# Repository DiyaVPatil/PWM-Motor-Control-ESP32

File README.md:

# ESP32 PWM Motor Controller
A custom PCB-based motor controller designed in KiCad for efficient PWM speed control of brushed DC motors using an ESP32 microcontroller.

This project began as a perfboard prototype and was later redesigned as a custom printed circuit board to improve physical dimensions and manufacturability.

## Features
- ESP32-based PWM motor control
- Adjustable motor speed (0–100% duty cycle)
- Logic-level MOSFET driver stage
- Flyback diode protection
- Battery-powered operation (3.7 V Li-ion)
- Compact custom PCB designed in KiCad

## Hardware
1) ESP32 DevKit | Main microcontroller 
2) IRLB8748 | Logic-level N-channel MOSFET 
3) Schottky Diode | Flyback protection 
4) TP4056 | Li-ion charging module 
5) 3.7 V Li-ion Battery | Portable power source 
6) Coreless DC Motor | Demonstration load 

## Project Timeline

### Version 1
Perfboard prototype built from KiCad schematic as a "proof-of-concept"

### Version 2
Final custom KiCad PCB, after making improvements from the perfboard prototype. 

## Future Improvements

- Real-time speed feedback on an OLED display
- Battery percentage monitoring
- Current sensing
- Bluetooth control
- Closed-loop speed control using encoder feedback

## Repository Structure
Note that there is a functionality video available under images and BOM
```
ESP32-PWM-Motor-Controller/

firmware/
hardware/
kicad/
images and BOM/
docs/
README.md
```

## Author

Diya

Electrical Engineering Student  
University of California, Riverside

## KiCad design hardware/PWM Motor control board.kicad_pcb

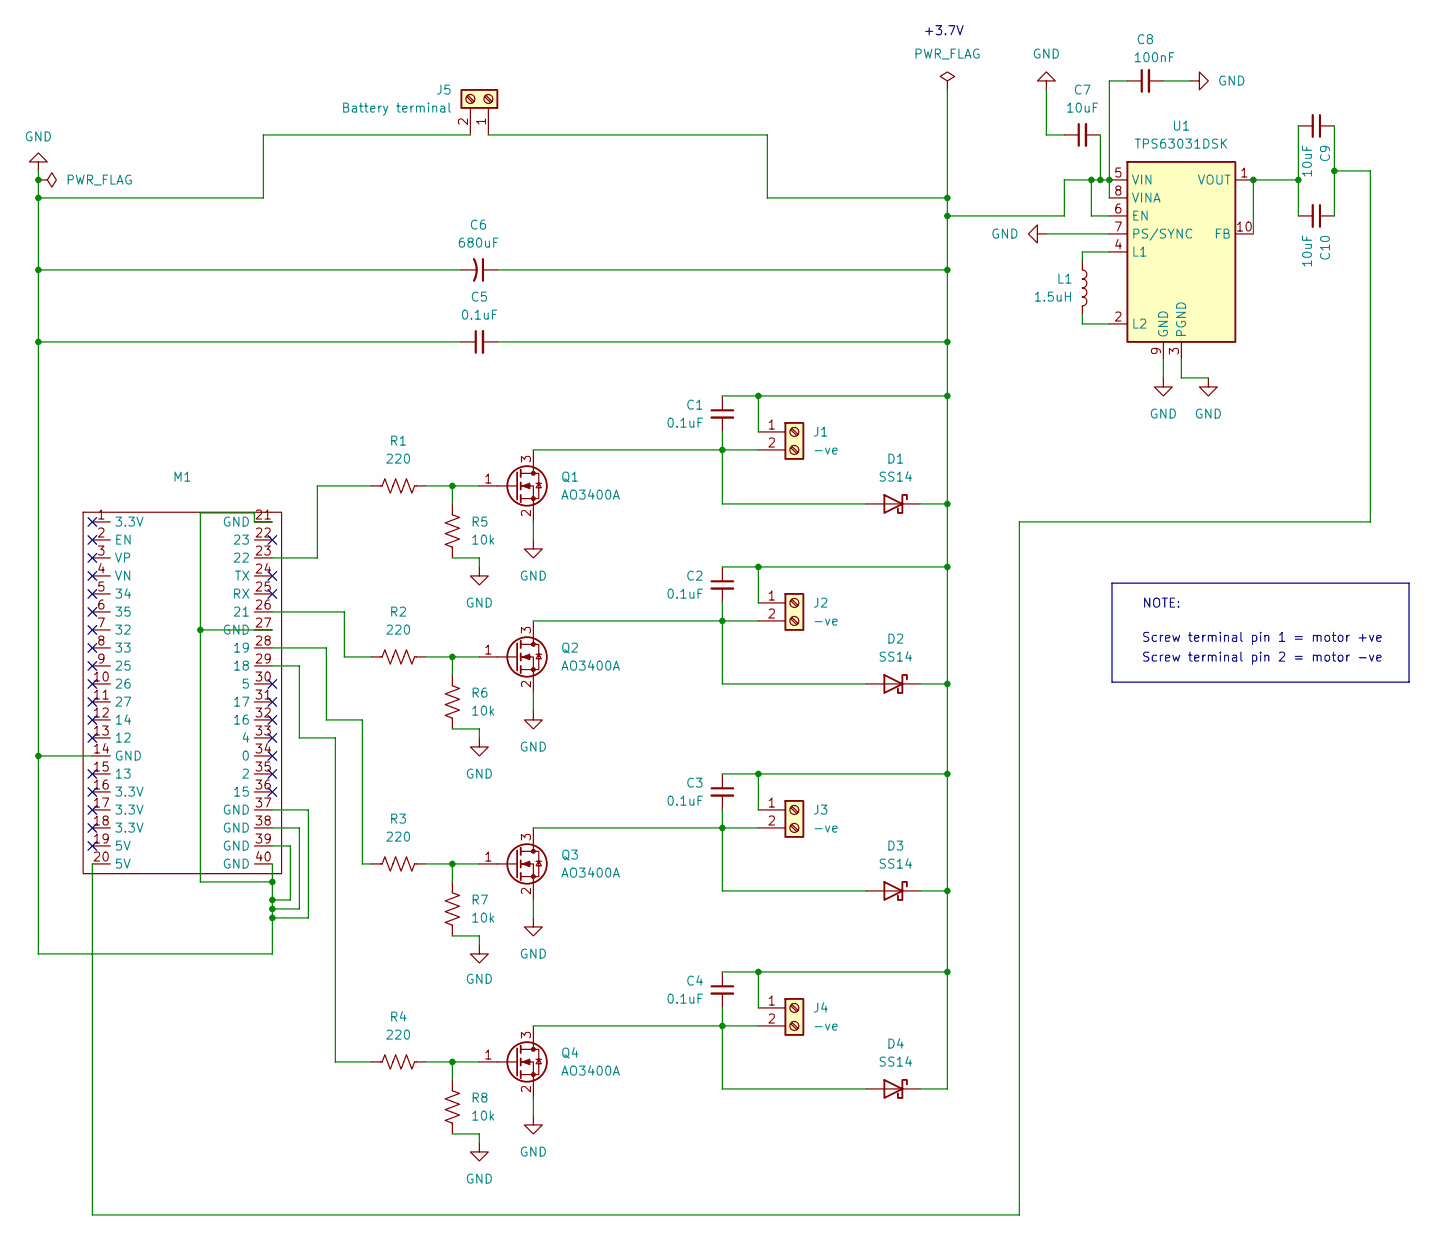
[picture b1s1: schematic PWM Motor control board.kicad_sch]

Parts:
C1, C2, C3, C4, C5: 0.1uF; C_0603_1608Metric
C6: 680uF; CP_Elec_8x10.5
C7, C9, C10: 10uF; C_0805_2012Metric
C8: 100nF; C_0603_1608Metric
D1, D2, D3, D4: SS14; D_SMA
J1, J2, J3, J4: -ve; TerminalBlock_Phoenix_PTSM-0,5-2-2,5-V-SMD_1x02-1MP_P2.50mm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
J5: Battery terminal; TerminalBlock_Phoenix_PTSM-0,5-2-2,5-V-SMD_1x02-1MP_P2.50mm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
L1: 1.5uH; L_Coilcraft_XxL4020
M1: Untitled
Q1, Q2, Q3, Q4: AO3400A; SOT-23
R1, R2, R3, R4: 220; R_0603_1608Metric
R5, R6, R7, R8: 10k; R_0603_1608Metric
U1: TPS63031DSK; WSON-10-1EP_2.5x2.5mm_P0.5mm_EP1.2x2mm

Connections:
GND: C5.1, C6.2, C7.1, C8.2, J5.2, M1.14 (GND), M1.21 (GND), M1.27 (GND), M1.37 (GND), M1.38 (GND), M1.39 (GND), M1.40 (GND), Q1.2 (S), Q2.2 (S), Q3.2 (S), Q4.2 (S), R5.2, R6.2, R7.2, R8.2, U1.3 (PGND), U1.7 (PS/SYNC), U1.9 (GND), U1.11 (PGND)
unnamed: C9.1, C10.1, M1.20 (5V)
unnamed: C1.2, D1.2 (A), J1.2, Q1.3 (D)
unnamed: C1.1, C2.1, C3.1, C4.1, C5.2, C6.1, C7.2, C8.1, D1.1 (K), D2.1 (K), D3.1 (K), D4.1 (K), J1.1, J2.1, J3.1, J4.1, J5.1, U1.5 (VIN), U1.6 (EN), U1.8 (VINA)
unnamed: C2.2, D2.2 (A), J2.2, Q2.3 (D)
unnamed: C3.2, D3.2 (A), J3.2, Q3.3 (D)
unnamed: C4.2, D4.2 (A), J4.2, Q4.3 (D)
unnamed: M1.29 (18), R4.1
unnamed: M1.28 (19), R3.1
unnamed: M1.26 (21), R2.1
unnamed: M1.23 (22), R1.1
unnamed: Q1.1 (G), R1.2, R5.1
unnamed: Q2.1 (G), R2.2, R6.1
unnamed: Q3.1 (G), R3.2, R7.1
unnamed: Q4.1 (G), R4.2, R8.1
unnamed: C9.2, C10.2, U1.1 (VOUT), U1.10 (FB)
unnamed: L1.2, U1.4 (L1)
unnamed: L1.1, U1.2 (L2)

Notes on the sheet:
Screw terminal pin 1 = motor +ve
+3.7V
Screw terminal pin 2 = motor -ve
NOTE:

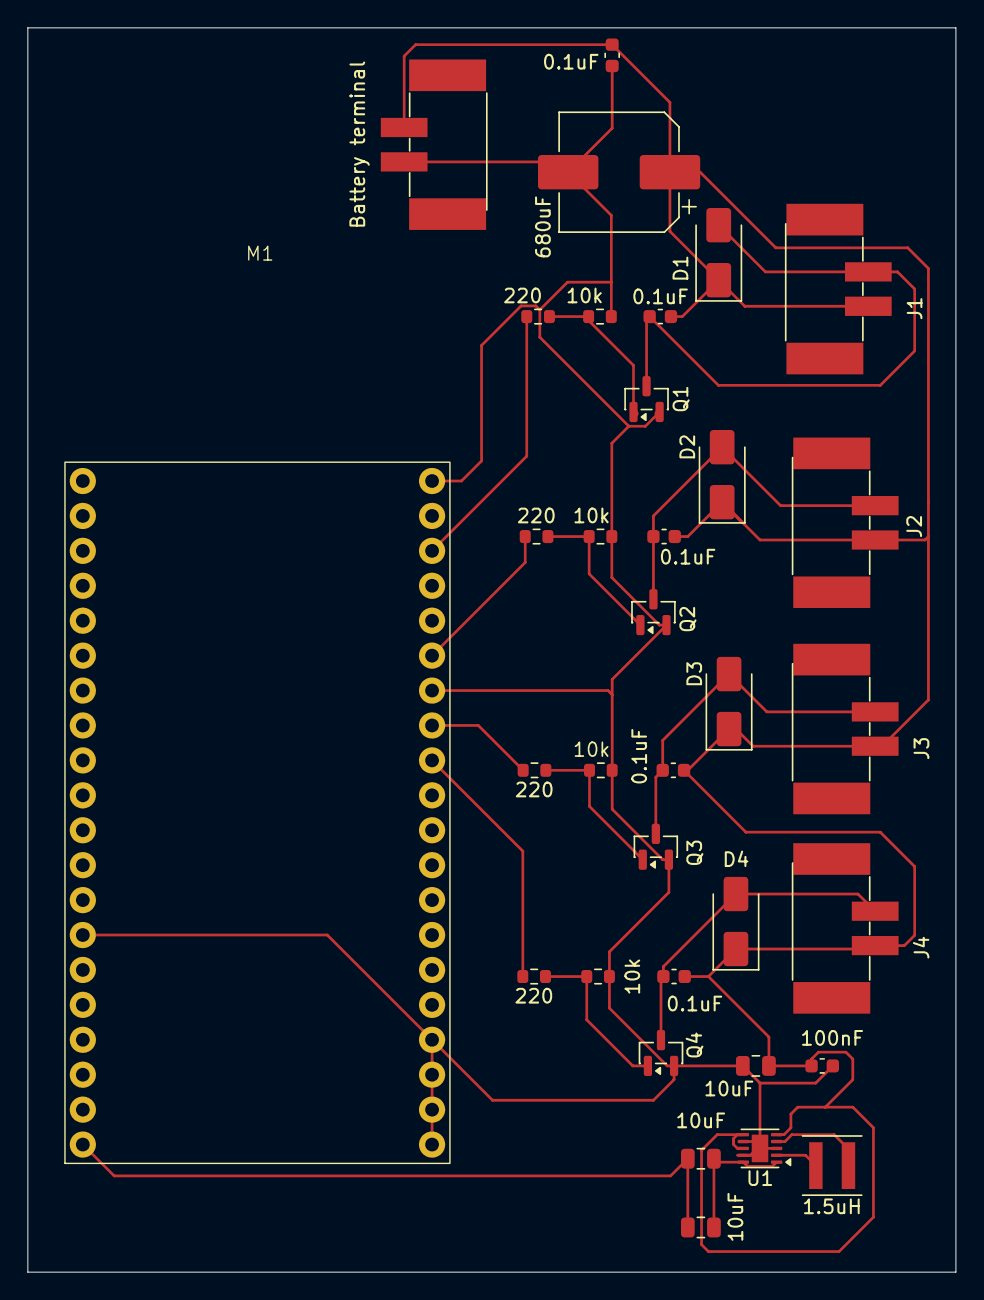
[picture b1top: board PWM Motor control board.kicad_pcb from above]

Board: 2 copper layers, 67.5 x 90.5 mm, 34 parts (0 on the bottom side), 18 nets.
